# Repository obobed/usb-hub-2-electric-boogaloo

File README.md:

# UEB2
## another usb hub!
I made this since I wanted a unique USB hub with cool colours unlike some bland and boring ones you find off Amazon or places like that. It has 2 USB-C, 1 USB-A and an Micro SD card slot for downstream ports, and a USB-C female port for the upstream, alongside a cool 3D printed case with cool accent colours and an acrylic top window.

## Repo Structure
When a directory includes a folder named "archive", that contains the files I used before I modified my PCB to use a female upstream port instead of a male one
* [/3D](/3D) - 3D models (both the components and the whole pcb exported as a STEP)
* [/cad](/cad) - my case exported from onshape (you can view the actual onshape link below), has both models with the PCB inside, and without the PCB
* [/images](/images) - various image assets used in my readme (here) and my zine!
* [/pcb](/pcb) - all of my kicad design files
* [/plots](/plots) - various plots, including dxfs for each layer, and a schematic image
* [/production](/production) - contains everything needed for PCB production, like gerbers and a component BOM
* [/rendering](/rendering) - the documents I used in Blender to render my design, with the OnShape exported objs in a subfolder
* [/zine](/zine) - my Zine! pdf and png included, and most assets are in [/images](/images)

## CAD
[OnShape link here!](https://cad.onshape.com/documents/3911889ee056a8d8e4ba98bf/w/b6e308ebfed3eeb37e65c26c/e/fc788076bb25bd97f4780c85?renderMode=0&uiState=6a2ab7df3cd020227a4c42b9)
Step files can be found in [/cad](cad/)

## Images
### Schematic

### 3D Model

### PCB

#### Front Copper

#### Back Copper

#### Silkscreen

## Assembly
### Top Acrylic Window
1. Print out the [top window template](/cad/acrylic-window-print-template.pdf) and stick it to your acrylic temporarily (using sticky tape or something like that)
2. Use a box cutter or acrylic cutter to score along the template
3. Snap along the score lines
4. Put a small amount of your adhesive (like Gorilla Gel) around the interior top lip
5. Place the acrylic ontop and wait a few minutes for it to set

> [!NOTE]
> I'm using glue here, since there aren't other good options that are fit in this size (like heatsets definitely won't) and wouldn't compromise the transparency of the acrylic

### PCB and Case
1. Get the heatset inserts and put them in the holes
2. Use a heated soldering iron to push them down until they're flush
3. Align the PCB with the holes
4. Screw the M2 screws in, and you're done!

## BOM
### OVERALL
|Item            |Quantity                        |Link|Cost ($) USD unless said otherwise|Notes   |
|----------------|--------------------------------|----|----------------------------------|--------|
|Heatset inserts |3                               |[aliexpress.com/item/1005006967339727](https://www.aliexpress.com/item/1005006967339727.html)|6.27 (AUD)                        |M2xL3xOD3.2 100pcs|
|Screws          |50                              |[aliexpress.com/item/32969042589](https://www.aliexpress.com/item/32969042589.html)|1.69 (AUD)                        |M2, Length 4mm, 50pcs is the MOQ, since obv you can't order individual screws|
|3D Printed Case |1                               |    |FREE (if you have a printer, which I do)|        |
|PCB             |5                               |[jlcpcb.com](https://jlcpcb.com)|4.00                              |        |
|PCBA            |2                               |[jlcpcb.com](https://jlcpcb.com)|47.54                             |        |
|PCB Shipping    |1                               |[jlcpcb.com](https://jlcpcb.com)|1.50                              |        |
|Acrylic         |1                               |[aliexpress.com/item/32817321651.html](https://www.aliexpress.com/item/32817321651.html)|2.99 (AUD)                        |100x100x2. If you need, get an acrylic cutter. I don't have one in this BOM as I have a box cutter and that works fine with this 2mm sheet. Additionally, if you don't already have an adhesive (like [Gorilla Super Glue Gel](https://www.bunnings.com.au/gorilla-20g-super-glue-gel_p0381626), you will have to get it, but it's not included here as I already have it|
|                |                                |    |                                  |        |
|TOTAL           |                                |    |53.04 USD + 10.95 AUD             |        |

### PCB Components
> [!IMPORTANT]
> **This is already included under 'PCBA' in the overall BOM, these are just the indivdual component costs, don't double count it**

|Designator      |Footprint                       |Quantity|Value           |LCSC Part #|Link                                                               |Cost ($)|
|----------------|--------------------------------|--------|----------------|-----------|-------------------------------------------------------------------|--------|
|C1, C4          |603                             |2       |4.7u            |C19666     |https://jlcpcb.com/partdetail/20375-CL10A475KO8NNNC/C19666         |0.184   |
|C10, C11, C8    |402                             |3       |100n            |C1525      |https://jlcpcb.com/partdetail/1877-CL05B104KO5NNNC/C1525           |0.0345  |
|C12, C9         |402                             |2       |1u              |C52923     |https://jlcpcb.com/partdetail/53938-CL05A105KA5NQNC/C52923         |0.069   |
|C13             |603                             |1       |1u              |C15849     |https://jlcpcb.com/partdetail/16531-CL10A105KB8NNNC/C15849         |0.079   |
|C14, C15, C2, C6|603                             |4       |10u             |C19702     |https://jlcpcb.com/partdetail/20411-CL10A106KP8NNNC/C19702         |0.346   |
|C3, C5          |603                             |2       |100n            |C14663     |https://jlcpcb.com/partdetail/YAGEO-CC0603KRX7R9BB104/C14663       |0.094   |
|C7              |402                             |1       |10u             |C15525     |https://jlcpcb.com/partdetail/16204-CL05A106MQ5NUNC/C15525         |0.093   |
|D1              |D_SOD-323                       |1       |1N5819WS        |C191023    |https://jlcpcb.com/partdetail/GuangdongHottech-1N5819WS/C191023    |0.0555  |
|D2, D3          |UDFN-9_L3.9-W1.1-P0.80-BL       |2       |RCLAMP3328P.TZT |C3040834   |https://jlcpcb.com/partdetail/SEMTECH-RCLAMP3328PTZT/C3040834      |8.191   |
|D4, D5, D6, D7  |SOD-523_L1.2-W0.8-LS1.6-RD      |4       |PESD5V0V1BB,115 |C477993    |https://jlcpcb.com/partdetail/Nexperia-PESD5V0V1BB115/C477993      |8.6925  |
|R1, R2, R3      |603                             |3       |10k             |C25804     |https://jlcpcb.com/partdetail/26547-0603WAF1002T5E/C25804          |0.021   |
|R10, R7, R8, R9 |603                             |4       |56K             |C23206     |https://jlcpcb.com/partdetail/23933-0603WAF5602T5E/C23206          |0.04    |
|R4              |402                             |1       |5K1             |C25905     |https://jlcpcb.com/partdetail/26648-0402WGF5101TCE/C25905          |0.0045  |
|R5, R6          |402                             |2       |10k             |C25744     |https://jlcpcb.com/partdetail/26487-0402WGF1002TCE/C25744          |0.028   |
|SIM1            |SIM-SMD_8P-1040310811           |1       |1040310811      |C585350    |https://jlcpcb.com/partdetail/MOLEX-1040310811/C585350             |3.37    |
|U1              |SSOP-16_L4.9-W3.9-P0.64-LS6.0-BL|1       |GL823K-HCY04    |C284879    |https://jlcpcb.com/partdetail/GenesysLogic-GL823KHCY04/C284879     |2.2815  |
|U2              |SSOP-16_L4.6-W2.6-P0.53-LS4.0-BL|1       |SL2.1S          |C2684433   |https://jlcpcb.com/partdetail/CoreChips-SL21s/C2684433             |1.253   |
|USB1, USB3, USB4|USB-C-SMD_TYPE-C-16PIN-2MD-073  |3       |TYPE-C 16PIN 2MD|C2765186   |https://jlcpcb.com/partdetail/SHOUHAN-TYPE_C_16PIN_2MD_073/C2765186|1.1776  |
|USB2            |USB-A-TH_10.0QHHTZB6.3          |1       |10.0 QHHTZB6.3  |C668591    |https://jlcpcb.com/partdetail/SHOUHAN-10_0_QHHTZB63/C668591        |0.4634  |
|                |                                |        |                |           |                                                                   |        |
|TOTAL           |                                |        |                |           |                                                                   |26.4775 |

## Zine!!

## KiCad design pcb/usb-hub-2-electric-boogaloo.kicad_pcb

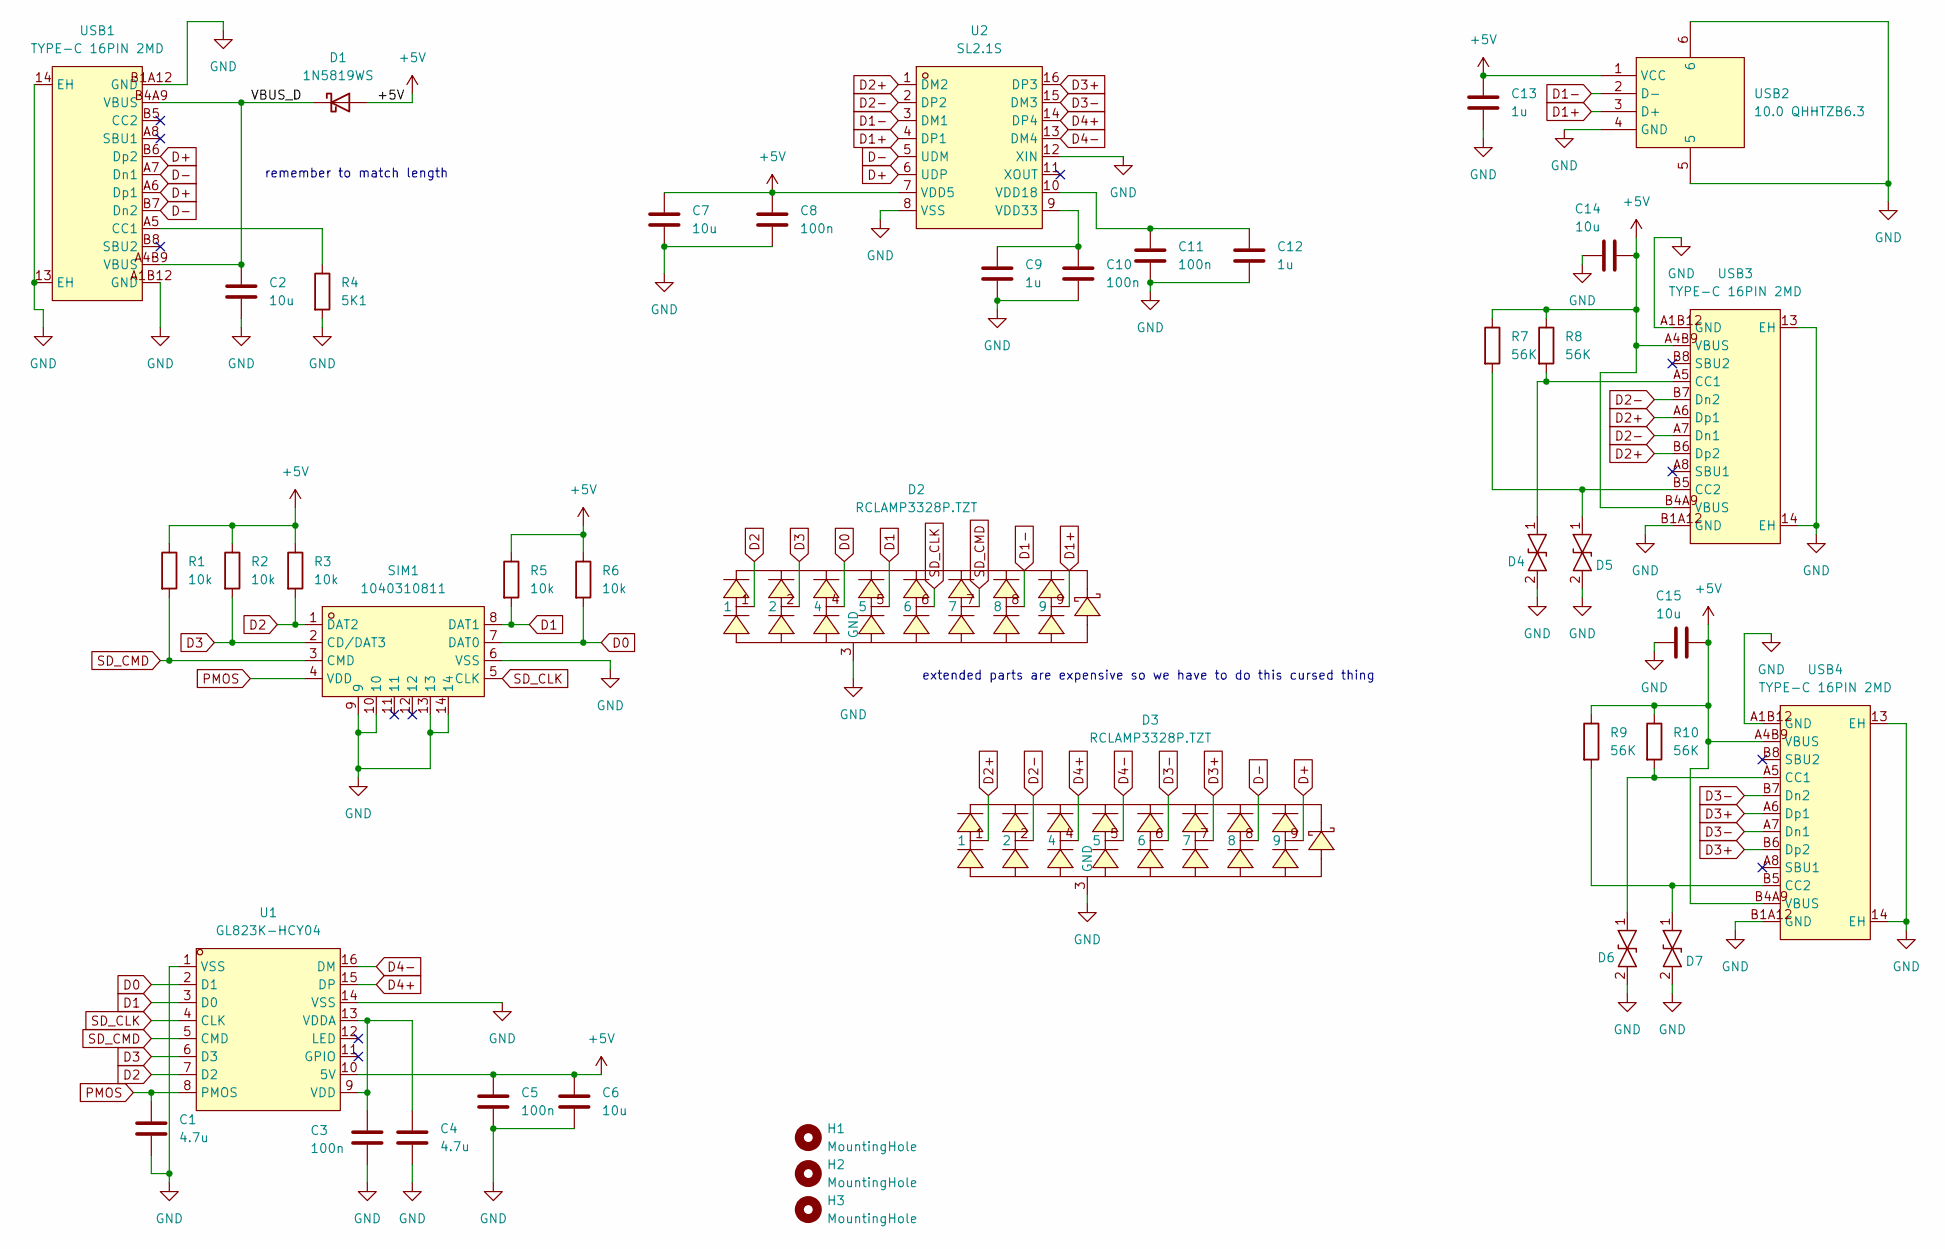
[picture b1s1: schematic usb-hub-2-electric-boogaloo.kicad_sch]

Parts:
C1, C4: 4.7u; C_0603_1608Metric_Pad1.08x0.95mm_HandSolder
C2, C6, C14, C15: 10u; C_0603_1608Metric_Pad1.08x0.95mm_HandSolder
C3, C5: 100n; C_0603_1608Metric_Pad1.08x0.95mm_HandSolder
C7: 10u; C_0402_1005Metric_Pad0.74x0.62mm_HandSolder
C8, C10, C11: 100n; C_0402_1005Metric_Pad0.74x0.62mm_HandSolder
C9, C12: 1u; C_0402_1005Metric_Pad0.74x0.62mm_HandSolder
C13: 1u; C_0603_1608Metric_Pad1.08x0.95mm_HandSolder
D1: 1N5819WS; D_SOD-323
D2, D3: RCLAMP3328P.TZT; UDFN-9_L3.9-W1.1-P0.80-BL; MPN RCLAMP3328P.TZT; LCSC Part C3040834
D4, D5, D6, D7: PESD5V0V1BB,115; SOD-523_L1.2-W0.8-LS1.6-RD; MPN PESD5V0V1BB,115; LCSC Part C477993
H1, H2, H3: MountingHole; MountingHole_2.2mm_M2
R1, R2, R3: 10k; R_0603_1608Metric_Pad0.98x0.95mm_HandSolder
R4: 5K1; R_0402_1005Metric_Pad0.72x0.64mm_HandSolder
R5, R6: 10k; R_0402_1005Metric_Pad0.72x0.64mm_HandSolder
R7, R8, R9, R10: 56K; R_0603_1608Metric_Pad0.98x0.95mm_HandSolder
SIM1: 1040310811; SIM-SMD_8P-1040310811; MPN 1040310811; LCSC Part C585350
U1: GL823K-HCY04; SSOP-16_L4.9-W3.9-P0.64-LS6.0-BL; LCSC Part C284879
U2: SL2.1S; SSOP-16_L4.6-W2.6-P0.53-LS4.0-BL; MPN SL2.1s; LCSC Part C2684433
USB1, USB3, USB4: TYPE-C 16PIN 2MD; USB-C-SMD_TYPE-C-16PIN-2MD-073; MPN TYPE-C 16PIN 2MD(073); LCSC Part C2765186
USB2: 10.0 QHHTZB6.3; USB-A-TH_10.0QHHTZB6.3; MPN 10.0 QHHTZB6.3; LCSC Part C668591

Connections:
+5V: C5.1, C6.1, C7.1, C8.1, C13.1, C14.1, C15.2, D1.2 (A), R1.1, R2.1, R3.1, R5.1, R6.1, R7.1, R8.1, R9.1, R10.1, U1.10 (5V), U2.7 (VDD5), USB2.1 (VCC), USB3.A4B9 (VBUS), USB3.B4A9 (VBUS), USB4.A4B9 (VBUS), USB4.B4A9 (VBUS)
/VBUS_D: C2.1, D1.1 (K), USB1.A4B9 (VBUS), USB1.B4A9 (VBUS)
D0: D2.4, R6.2, SIM1.7 (DAT0), U1.2 (D1)
D1: D2.5, R5.2, SIM1.8 (DAT1), U1.3 (D0)
D1+: D2.9, U2.4 (DP1), USB2.3 (D+)
D1-: D2.8, U2.3 (DM1), USB2.2 (D-)
D2: D2.1, R3.2, SIM1.1 (DAT2), U1.7 (D2)
D2+: D3.1, U2.1 (DM2), USB3.A6 (Dp1), USB3.B6 (Dp2)
D2-: D3.2, U2.2 (DP2), USB3.A7 (Dn1), USB3.B7 (Dn2)
D3: D2.2, R2.2, SIM1.2 (CD/DAT3), U1.6 (D3)
D3+: D3.7, U2.16 (DP3), USB4.A6 (Dp1), USB4.B6 (Dp2)
D3-: D3.6, U2.15 (DM3), USB4.A7 (Dn1), USB4.B7 (Dn2)
D4+: D3.4, U1.15 (DP), U2.14 (DP4)
D4-: D3.5, U1.16 (DM), U2.13 (DM4)
D+: D3.9, U2.6 (UDP), USB1.A6 (Dp1), USB1.B6 (Dp2)
D-: D3.8, U2.5 (UDM), USB1.A7 (Dn1), USB1.B7 (Dn2)
GND: C1.2, C2.2, C3.1, C4.2, C5.2, C6.2, C7.2, C8.2, C9.2, C10.2, C11.2, C12.2, C13.2, C14.2, C15.1, D2.3 (GND), D3.3 (GND), D4.2, D5.2, D6.2, D7.2, R4.2, SIM1.6 (VSS), SIM1.9, SIM1.10, SIM1.13, SIM1.14, U1.1 (VSS), U1.14 (VSS), U2.8 (VSS), U2.12 (XIN), USB1.13 (EH), USB1.14 (EH), USB1.A1B12 (GND), USB1.B1A12 (GND), USB2.4 (GND), USB2.5, USB2.6, USB3.13 (EH), USB3.14 (EH), USB3.A1B12 (GND), USB3.B1A12 (GND), USB4.13 (EH), USB4.14 (EH), USB4.A1B12 (GND), USB4.B1A12 (GND)
unnamed: C3.2, C4.1, U1.9 (VDD), U1.13 (VDDA)
unnamed: C11.1, C12.1, U2.10 (VDD18)
unnamed: C9.1, C10.1, U2.9 (VDD33)
unnamed: R4.1, USB1.A5 (CC1)
unnamed: D4.1, R8.2, USB3.A5 (CC1)
unnamed: D5.1, R7.2, USB3.B5 (CC2)
unnamed: D6.1, R10.2, USB4.A5 (CC1)
unnamed: D7.1, R9.2, USB4.B5 (CC2)
PMOS: C1.1, SIM1.4 (VDD), U1.8 (PMOS)
SD_CLK: D2.6, SIM1.5 (CLK), U1.4 (CLK)
SD_CMD: D2.7, R1.2, SIM1.3 (CMD), U1.5 (CMD)

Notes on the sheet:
extended parts are expensive so we have to do this cursed thing
remember to match length

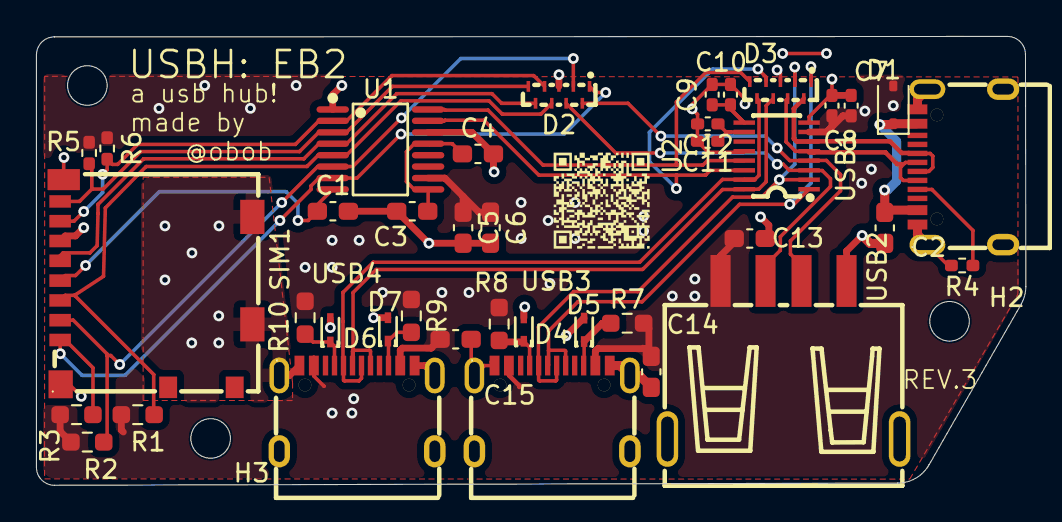
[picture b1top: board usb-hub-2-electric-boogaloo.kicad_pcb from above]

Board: 2 copper layers, 55.0 x 24.9 mm, 42 parts (0 on the bottom side), 28 nets.

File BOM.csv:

PCB COMPONENT BOM,,,,,,
Designator,Footprint,Quantity,Value,LCSC Part #,Link,Cost ($)
"C1, C4",603,2,4.7u,C19666,https://jlcpcb.com/partdetail/20375-CL10A475KO8NNNC/C19666,0.184
"C10, C11, C8",402,3,100n,C1525,https://jlcpcb.com/partdetail/1877-CL05B104KO5NNNC/C1525,0.0345
"C12, C9",402,2,1u,C52923,https://jlcpcb.com/partdetail/53938-CL05A105KA5NQNC/C52923,0.069
C13,603,1,1u,C15849,https://jlcpcb.com/partdetail/16531-CL10A105KB8NNNC/C15849,0.079
"C14, C15, C2, C6",603,4,10u,C19702,https://jlcpcb.com/partdetail/20411-CL10A106KP8NNNC/C19702,0.346
"C3, C5",603,2,100n,C14663,https://jlcpcb.com/partdetail/YAGEO-CC0603KRX7R9BB104/C14663,0.094
C7,402,1,10u,C15525,https://jlcpcb.com/partdetail/16204-CL05A106MQ5NUNC/C15525,0.093
D1,D_SOD-323,1,1N5819WS,C191023,https://jlcpcb.com/partdetail/GuangdongHottech-1N5819WS/C191023,0.0555
"D2, D3",UDFN-9_L3.9-W1.1-P0.80-BL,2,RCLAMP3328P.TZT,C3040834,https://jlcpcb.com/partdetail/SEMTECH-RCLAMP3328PTZT/C3040834,8.191
"D4, D5, D6, D7",SOD-523_L1.2-W0.8-LS1.6-RD,4,"PESD5V0V1BB,115",C477993,https://jlcpcb.com/partdetail/Nexperia-PESD5V0V1BB115/C477993,8.6925
"R1, R2, R3",603,3,10k,C25804,https://jlcpcb.com/partdetail/26547-0603WAF1002T5E/C25804,0.021
"R10, R7, R8, R9",603,4,56K,C23206,https://jlcpcb.com/partdetail/23933-0603WAF5602T5E/C23206,0.04
R4,402,1,5K1,C25905,https://jlcpcb.com/partdetail/26648-0402WGF5101TCE/C25905,0.0045
"R5, R6",402,2,10k,C25744,https://jlcpcb.com/partdetail/26487-0402WGF1002TCE/C25744,0.028
SIM1,SIM-SMD_8P-1040310811,1,1040310811,C585350,https://jlcpcb.com/partdetail/MOLEX-1040310811/C585350,3.37
U1,SSOP-16_L4.9-W3.9-P0.64-LS6.0-BL,1,GL823K-HCY04,C284879,https://jlcpcb.com/partdetail/GenesysLogic-GL823KHCY04/C284879,2.2815
U2,SSOP-16_L4.6-W2.6-P0.53-LS4.0-BL,1,SL2.1S,C2684433,https://jlcpcb.com/partdetail/CoreChips-SL21s/C2684433,1.253
"USB1, USB3, USB4",USB-C-SMD_TYPE-C-16PIN-2MD-073,3,TYPE-C 16PIN 2MD,C2765186,https://jlcpcb.com/partdetail/SHOUHAN-TYPE_C_16PIN_2MD_073/C2765186,1.1776
USB2,USB-A-TH_10.0QHHTZB6.3,1,10.0 QHHTZB6.3,C668591,https://jlcpcb.com/partdetail/SHOUHAN-10_0_QHHTZB63/C668591,0.4634
TOTAL,,,,,,26.4775
,,,,,,
OVERALL BOM,,,,,,
Item,Quantity,Link,Cost ($) USD unless said otherwise,Notes,,
Heatset inserts,3,https://www.aliexpress.com/item/1005006967339727.html,6.27 (AUD),M2xL3xOD3.2 100pcs,,
Screws,50,aliexpress.com/item/32969042589.html,1.69 (AUD),"M2, Length 4mm, 50pcs is the MOQ, since obv you can't order individual screws",,
3D Printed Case,1,,FREE (if you have a printer),,,
PCB,5,jlcpcb.com,4.00,,,
PCBA,2,jlcpcb.com,47.54,,,
PCB Shipping,1,jlcpcb.com,1.50,,,
Acrylic,1,https://www.aliexpress.com/item/32817321651.html,2.99 (AUD),"100x100x2. If you need, get an acrylic cutter. I don't have one here as I have a box cutter and that works fine with this 2mm sheet",,
,,,,,,
TOTAL,,,53.04 USD + 10.95 AUD,,,

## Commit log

2026-05-27 schema except for sd bc that takes time
2026-05-27 probably messed something up, but schema done!
2026-05-30 fixing schema + lots of esd protection
2026-05-30 fixed some stuff
    schottky + more decoupling caps
2026-06-01 pcb layout + revise usb-c schema
2026-06-01 some (bad) routing
2026-06-02 routing traces
2026-06-05 finish main routing (still disconnects tho)
2026-06-06 vias and mounting holes
2026-06-06 whoops drc exists
2026-06-08 dxf + fixed 3D view + silkscreen
2026-06-11 zine + cad case + renders
2026-06-11 blender saved??
2026-06-11 notdone!!
2026-06-12 fix usb + new renders
2026-06-12 basic readme, need more intro and conclusion and glue/adhesive for acrylic (also aliexpress)
2026-06-12 restructure folders
    get rid of the unnecessary nested folder
2026-06-12 rename 3d folder so i can link in readme
2026-06-12 move image assets to better location
2026-06-12 add pcb and schema images
2026-06-12 update rev and add 3D back image
2026-06-12 improve readme with CAD, images, and BOM sections
2026-06-13 add pdf template for the top acrylic window
2026-06-13 update bom, add more images and assembly steps
2026-06-13 add zine to readme
2026-06-13 add case assembly instructions
